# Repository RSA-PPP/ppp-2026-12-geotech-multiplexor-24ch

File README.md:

# ppp-2026-13-geotech-multiplexor-24ch

> **Red Sísmica del Austro (RSA) — Universidad de Cuenca**  
> Prácticas Preprofesionales (PPP) • Sistemas Embebidos, Instrumentación Geotécnica y Control Electromecánico

---

## 📋 Ficha Técnica del Proyecto

| Campo | Detalle |
| :--- | :--- |
| **Código Institucional** | `RSA-PPP-2026-13` |
| **Nombre del Proyecto** | Sistema de Adquisición Electromecánico Multiplexado para Galgas Extensométricas en Presas (ESP32 y PIC16F628A) |
| **Pasante** | Walter Calderón (`walter.calderon@ucuenca.edu.ec`) |
| **Carrera / Institución** | Ingeniería en Telecomunicaciones — Universidad de Cuenca |
| **Tutor Institucional** | Ing. Milton Muñoz (`milton.munozc@ucuenca.edu.ec`) — RSA |
| **Duración / Horas** | 144 horas (10.5 semanas) • Presencial |
| **Fecha de Ejecución** | 2026-10-01 al 2026-12-18 |
| **Estado** | `En Ejecución` |

---

## 🎯 Descripción General y Objetivos

La Red Sísmica del Austro (RSA) gestiona la auscultación estructural continua de presas hidroeléctricas críticas (como Chanlud y Labrado), donde la monitorización de la estabilidad del cuerpo de presa depende de redes de **galgas extensométricas de 4 hilos** embebidas en el concreto y galerías. Cada sensor entrega dos variables físicas acopladas: **deformación mecánica ($\mu\varepsilon$)** y **temperatura interna ($^\circ\text{C}$)** para compensación térmica.

Para optimizar costos de instrumental analógico de ultra alta resolución, el sistema utiliza un mecanismo de multiplexación electromecánica compuesto por **dos selectores rotativos mecánicos de 12 canales** (totalizando 24 sensores analógicos). Cada selector es gobernado por un motor DC acoplado a encoders ópticos de ranura y referencia absoluta (*Home*). La conmutación entre el modo de deformación y el modo de temperatura se realiza mediante un banco de relés (K1..K5) que reconfigura un puente de Wheatstone conectado al convertidor analógico-digital de 24 bits **HX711**.

Este proyecto implementa una arquitectura distribuida de firmware resiliente y de alta precisión:
* **Controlador Esclavo (Microchip PIC16F628A):** Firmware en C (XC8) para posicionamiento angular determinista por interrupciones, frenado dinámico activo en puente H L293D y parser binario UART a 9600 bps.
* **Nodo Maestro de Gestión (Espressif ESP32-WROOM-32):** Firmware en C++ (PlatformIO) para lectura del HX711, secuenciamiento de relés con tiempos muertos de guarda ($\ge 20\text{ ms}$), datalogger autónomo en MicroSD (FAT32/CSV), pantalla LCD alfanumérica y telemetría por comandos ASCII vía RS-232 (115200 bps).

### Objetivos Clave
1. **Hardware y Diagnóstico de Encoders:** Auditar en osciloscopio las señales digitales de los encoders de ranura y muesca Home, y caracterizar las formas de onda de conmutación del puente H L293D.
2. **Firmware de Posicionamiento (PIC16F628A):** Desarrollar en MPLAB X / XC8 las rutinas de búsqueda de origen (*Homing*), conteo de ranuras por interrupciones y frenado dinámico asistido para evitar deslizamientos por inercia.
3. **Protocolo Inter-Microcontroladores:** Diseñar el enlace serie UART binario robusto con delimitadores y suma de comprobación XOR a 9600 bps con máquina de reintentos y tolerancia a fallos.
4. **Adquisición HX711 y Reconfiguración de Puente:** Desarrollar el driver de lectura diferencial de 24 bits para el HX711 y el secuenciador de relés K1..K5 con tiempos de estabilización (*dead-time* $\ge 20\text{ ms}$).
5. **Datalogger MicroSD, Interfaz LCD y Telemetría RS-232:** Implementar la persistencia local en `DATALOG.CSV`, la pantalla informativa LCD y el protocolo de telemetría exterior compatible con sistemas SCADA.
6. **Barrido Secuencial de 24 Canales y Ensayo en Banco:** Orquestar el ciclo completo de auscultación ($\le 90\text{ s}$ para 24 canales) y evaluar la resiliencia en un ensayo de 100 barridos continuos con resistencias patrón.
7. **Guía de Troubleshooting y Documentación Final:** Redactar el manual de solución de averías electromecánicas e Informe Técnico Final.

> 📄 Para consultar el cronograma detallado semana a semana, la carga horaria y los checkpoints verificables, revisa el [Plan de Trabajo Oficial](docs/planificacion.md).

---

## 🏗️ Arquitectura del Sistema y Flujo de Trabajo

```text
+-----------------------------------------------------------------------------------+
|                        DIAGRAMA DE ARQUITECTURA DISTRIBUIDA                       |
+-----------------------------------------------------------------------------------+
|                                                                                   |
|  [24 Galgas Extensométricas en Presa]                                            |
|         |                                                                         |
|         v                                                                         |
|  [Selectores Rotativos Electromecánicos M1 y M2 (12 canales c/u)]                 |
|         ^                                                                         |
|         | (Acoplamiento Mecánico)                                                 |
|  [2x Motores DC con Encoders Ópticos (sens1 / sens2_Home)]                       |
|         ^                                                                         |
|         | (Driver H-Bridge L293D con Frenado Dinámico)                            |
|  [Microchip PIC16F628A - Esclavo de Motores]                                      |
|         ^                                                                         |
|         | (Enlace UART Binario @ 9600 bps / Checksum XOR)                         |
|         v                                                                         |
|  [Espressif ESP32 - Maestro de Adquisición y Gestión]                             |
|  ├── Secuenciador de Relés K1..K5 (Dead-time >= 20 ms) ---> [Puente Wheatstone]   |
|  ├── Driver ADC Diferencial 24-bit (HX711) <----------------+                     |
|  ├── Datalogger Autónomo MicroSD (Bus SPI / FAT32 / DATALOG.CSV)                  |
|  ├── Interfaz de Operación Local (Pantalla LCD Alfanumérica)                      |
|  └── Puerto Serie de Telemetría RS-232 / SCADA ASCII @ 115200 bps                 |
+-----------------------------------------------------------------------------------+
```

---

## 📂 Estructura del Repositorio

> [!IMPORTANT]
> **Estructura Raíz Inmutable:** Para mantener la coherencia con los lineamientos de la RSA, la estructura de carpetas raíz no debe ser alterada ni renombrada sin previa coordinación con el tutor.

```text
ppp-2026-13-geotech-multiplexor-24ch/
├── data/
│   ├── evidence/              # Capturas oscilográficas, evidencias de frenado y curvas
│   └── raw_samples/           # Volcados de prueba de tarjetas MicroSD (DATALOG.CSV)
│
├── docs/
│   ├── hardware/              # Esquemáticos de placas de relés, motores y pinouts
│   ├── troubleshooting/       # Bitácora de fallas mecánicas, atascos y calibración
│   └── planificacion.md       # Documento rector del plan de trabajo (144h) y checkpoints
│
├── firmware/
│   ├── common/                # Definiciones de tramas binarias UART y constantes globales
│   ├── drivers/               # Librerías de bajo nivel: HX711, LCD, L293D, MicroSD
│   ├── pic16f628a/            # Proyecto MPLAB X / XC8 para control de motores
│   ├── esp32/                 # Proyecto PlatformIO / C++ maestro de adquisición
│   └── tests/                 # Firmwares de verificación de reloj, relés y encoders
│
├── python/
│   ├── scripts/               # Scripts de monitoreo RS-232 y parser de DATALOG.CSV
│   ├── utils/                 # Utilitarios para cálculo de estadísticas y verificación
│   └── requirements.txt       # Dependencias de Python para herramientas de soporte PC
│
├── README.md                  # Este documento
└── .gitignore                 # Exclusiones de Git (MPLAB X, PlatformIO, Python, SO)
```

---

## 🛠️ Herramientas y Requisitos de Desarrollo

* **Hardware / Instrumental:**
  - Microcontroladores Microchip **PIC16F628A** y módulo Espressif **ESP32-WROOM-32**.
  - Programador Microchip **PICkit 3 / 4** o **SNAP** con interfaz ICSP.
  - Driver H-Bridge **L293D** y banco de relés conmutadores K1..K5.
  - ADC diferencial de 24 bits **HX711** y módulo MicroSD SPI.
  - Osciloscopio digital, analizador lógico de 8 canales y multímetro de banco.
  - Caja de décadas de resistencias patrón ($350\,\Omega$ y $120\,\Omega \pm 0.05\%$).
* **Entornos de Desarrollo e IDEs:**
  - **MPLAB X IDE v6.xx** con compilador **Microchip XC8** para el PIC16F628A.
  - **VS Code + PlatformIO** (o ESP-IDF / Arduino Core) para el ESP32.
* **Herramientas de Soporte PC:**
  - Python 3.10+ en entorno virtual (`.venv`):
    ```bash
    pip install -r python/requirements.txt
    ```

---

## 🚀 Puesta en Marcha

### 1. Clonar el Repositorio
```bash
git clone git@github.com-rsa:RSA-PPP/ppp-2026-13-geotech-multiplexor-24ch.git
cd ppp-2026-13-geotech-multiplexor-24ch
```

### 2. Compilación del Firmware del Esclavo (PIC16F628A)
1. Abrir **MPLAB X IDE**.
2. Abrir el proyecto ubicado en `firmware/pic16f628a/`.
3. Seleccionar el compilador **XC8** y la herramienta de programación (**PICkit 3/4**).
4. Compilar (`Clean and Build`) y programar la tarjeta de control de motores vía ICSP.

### 3. Compilación del Firmware del Maestro (ESP32)
1. Abrir **VS Code** con la extensión **PlatformIO**.
2. Abrir la carpeta `firmware/esp32/`.
3. Compilar el proyecto (`PlatformIO: Build`) y subir al módulo vía puerto serie (`PlatformIO: Upload`).

### 4. Herramientas de PC y Telemetría RS-232
```powershell
python -m venv .venv
.\.venv\Scripts\Activate.ps1
pip install -r python/requirements.txt
python python/scripts/scada_monitor.py
```

---

## 🛡️ Reglas de Trabajo y Control de Versiones

Para asegurar la calidad y trazabilidad del proyecto durante las prácticas:

1. **Rama Principal:** La rama activa de trabajo es **`main`**. Realiza commits frecuentes y atómicos al finalizar cada bloque o jornada de trabajo.
2. **Formato de Commits:** Utiliza la convención estándar en minúsculas:
   - `feat: [nueva funcionalidad, driver o máquina de estados implementada]`
   - `fix: [corrección de bug en firmware, protocolo o circuito]`
   - `docs: [actualización de esquemas, pinouts, troubleshooting o informe]`
   - `test: [pruebas de encoders, oscilogramas o calibración con resistencias patrón]`
   - `refactor: [optimización de temporizaciones sin cambio de comportamiento]`
3. **Integridad de Código:** No subas archivos temporales de compilación (`.o`, `.d`, carpetas `build/`, `.pio/`) ni volcados masivos sin comprimir. Apóyate en el archivo `.gitignore`.

---

## 📞 Contacto y Soporte Institucional

* **Tutor Institucional:** Ing. Milton Muñoz (`milton.munozc@ucuenca.edu.ec`)
* **Institución:** [Red Sísmica del Austro (RSA)](https://redsismicaaustro.github.io/RSA-Metodologias) — Universidad de Cuenca

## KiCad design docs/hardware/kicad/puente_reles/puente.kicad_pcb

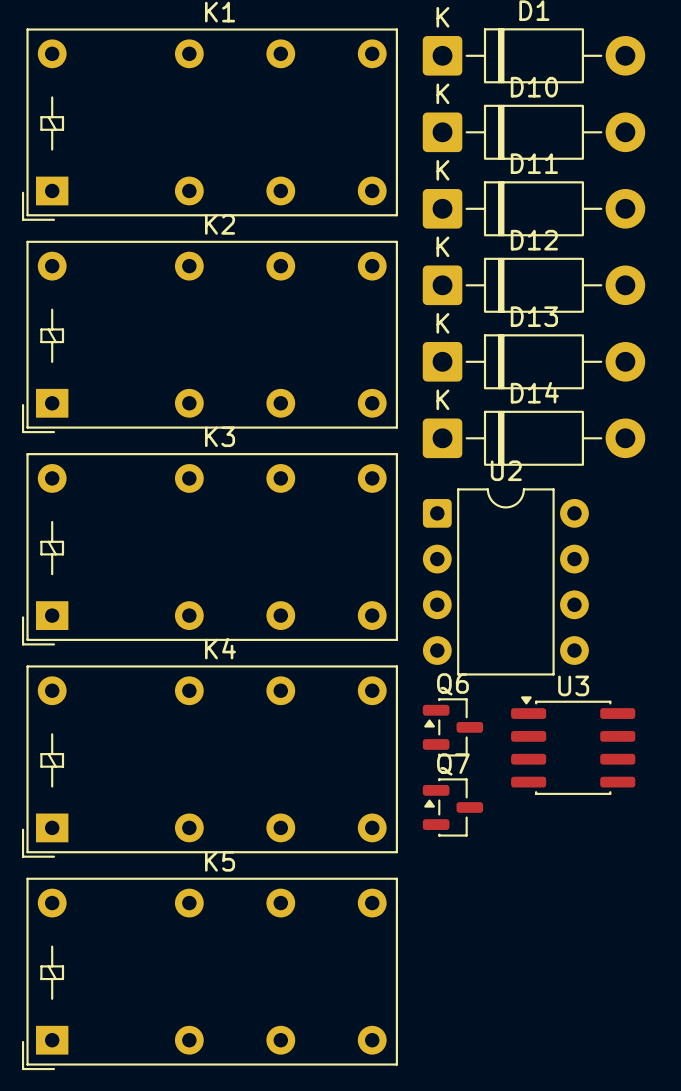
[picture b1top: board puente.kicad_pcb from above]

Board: 2 copper layers, 15 parts (0 on the bottom side), 14 nets, no tracks yet.

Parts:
D1, D10, D11, D12, D13, D14: 1N4007; D_DO-41_SOD81_P10.16mm_Horizontal
K1, K2, K3, K4, K5: HK19F-DCxxV-SHC; Relay_DPDT_Finder_30.22
Q6, Q7: BSS138; SOT-23
U2: DS1307+; DIP-8_W7.62mm
U3: MAX483E; SOIC-8_3.9x4.9mm_P1.27mm

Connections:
/+5V: U2.8 (VCC), U3.8 (VCC)
/+12V: D10.1 (K), D11.1 (K), D12.1 (K), D13.1 (K), D14.1 (K), K1.A1, K2.A1, K3.A1, K4.A1, K5.A1
/IN-: K4.12, K4.24
GND: U2.4 (GND), U3.5 (GND)
unnamed: D10.2 (A), K1.A2
unnamed: D11.2 (A), K2.A2
unnamed: D12.2 (A), K3.A2
unnamed: D13.2 (A), K4.A2
unnamed: D14.2 (A), K5.A2
unnamed: K2.24, K4.22
unnamed: K3.14, K5.11
unnamed: Q6.3 (D), U2.5 (SDA)
unnamed: Q7.3 (D), U2.6 (SCL)
VDD: D1.2 (A), K2.21, Q6.1 (G), Q7.1 (G)

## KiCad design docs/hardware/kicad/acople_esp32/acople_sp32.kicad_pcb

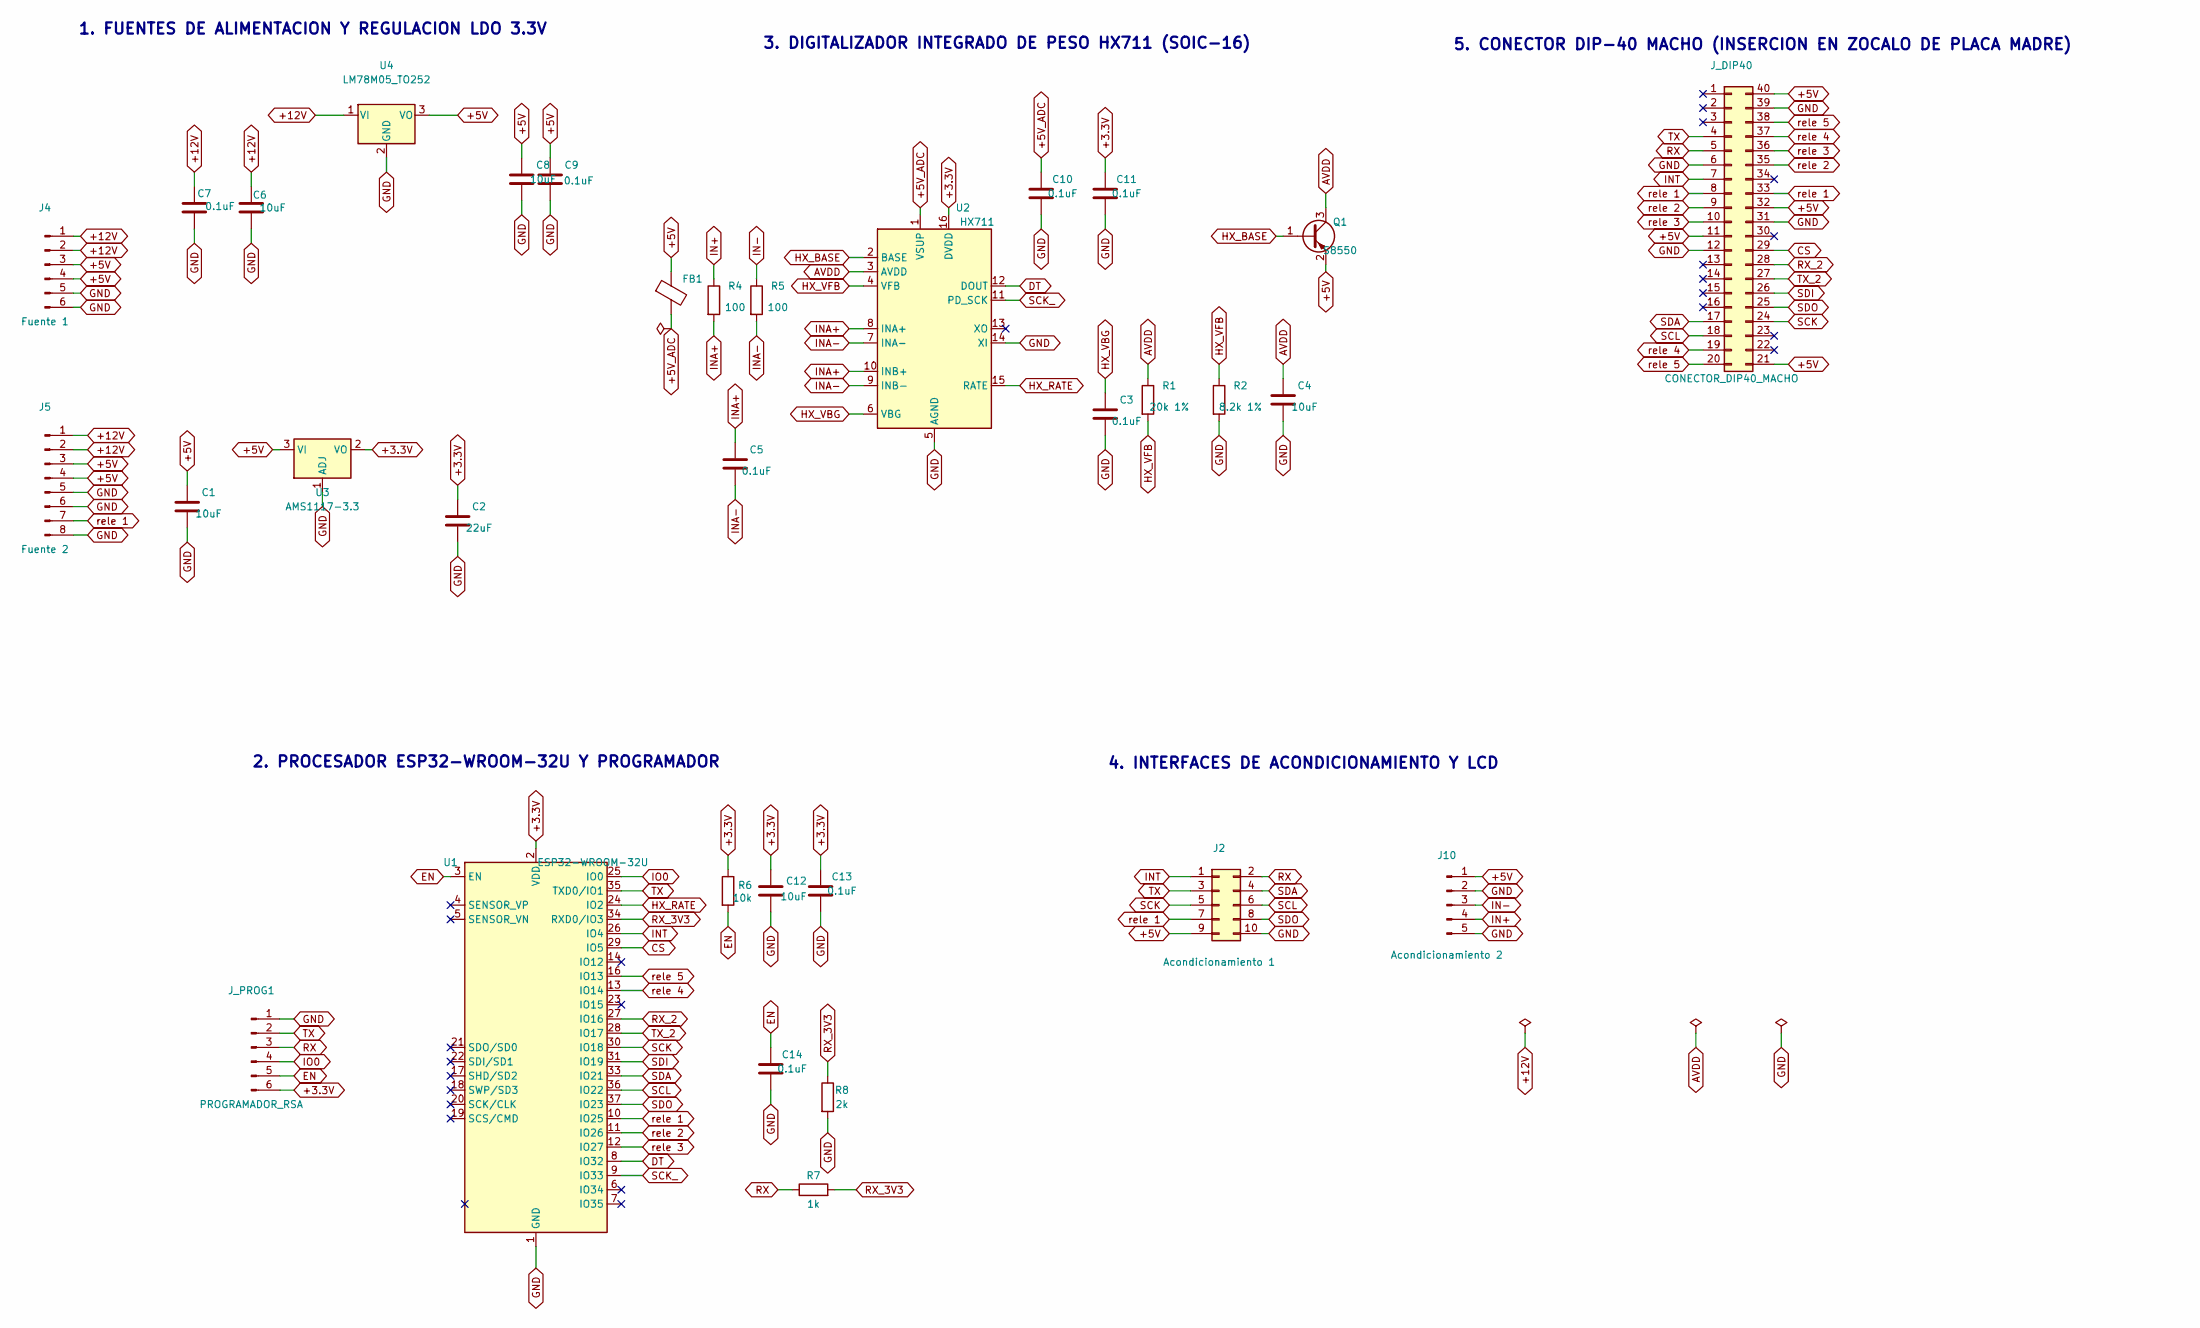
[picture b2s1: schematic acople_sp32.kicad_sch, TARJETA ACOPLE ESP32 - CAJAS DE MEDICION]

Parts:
C1, C4, C6, C8, C12: 10uF; C_0805_2012Metric
C2: 22uF; C_0805_2012Metric
C3, C5, C7, C9, C10, C11, C13, C14: 0.1uF; C_0805_2012Metric
FB1: 600R@100MHz; L_0805_2012Metric
J2: Acondicionamiento 1; PinHeader_2x05_P2.54mm_Vertical
J4: Fuente 1; PinHeader_1x06_P2.54mm_Vertical
J5: Fuente 2; PinHeader_1x08_P2.54mm_Vertical
J10: Acondicionamiento 2; PinHeader_1x05_P2.54mm_Vertical
J_DIP40: CONECTOR_DIP40_MACHO; DIP-40_W15.24mm
J_PROG1: PROGRAMADOR_RSA; PinHeader_1x06_P2.54mm_Vertical
Q1: S8550; SOT-23
R1: 20k 1%; R_0805_2012Metric
R2: 8.2k 1%; R_0805_2012Metric
R4, R5: 100; R_0805_2012Metric
R6: 10k; R_0805_2012Metric
R7: 1k; R_0805_2012Metric
R8: 2k; R_0805_2012Metric
U1: ESP32-WROOM-32U
U2: HX711; SOIC-16_3.9x9.9mm_P1.27mm
U3: AMS1117-3.3; SOT-223-3_TabPin2
U4: LM78M05_TO252; TO-252-3_TabPin2

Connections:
+3.3V: C2.1, C11.1, C12.1, C13.1, J_PROG1.6, R6.1, U1.2 (VDD), U2.16 (DVDD), U3.2 (VO)
+5V: C1.1, C8.1, C9.1, FB1.1, J2.9, J4.3, J4.4, J5.3, J5.4, J10.1, J_DIP40.11, J_DIP40.21, J_DIP40.32, J_DIP40.40, Q1.2 (E), U3.3 (VI), U4.3 (VO)
+5V_ADC: C10.1, FB1.2, U2.1 (VSUP)
+12V: C6.1, C7.1, J4.1, J4.2, J5.1, J5.2, U4.1 (VI)
AVDD: C4.1, Q1.3 (C), R1.1, U2.3 (AVDD)
CS: J_DIP40.29, U1.29 (IO5)
DT: U1.8 (IO32), U2.12 (DOUT)
EN: C14.1, J_PROG1.5, R6.2, U1.3 (EN)
GND: C1.2, C2.2, C3.2, C4.2, C6.2, C7.2, C8.2, C9.2, C10.2, C11.2, C12.2, C13.2, C14.2, J2.10, J4.5, J4.6, J5.5, J5.6, J5.8, J10.2, J10.5, J_DIP40.6, J_DIP40.12, J_DIP40.31, J_DIP40.39, J_PROG1.1, R2.2, R8.2, U1.1 (GND), U1.15 (GND), U1.38 (GND), U1.39 (GND), U2.5 (AGND), U2.14 (XI), U3.1 (ADJ), U4.2 (GND)
HX_BASE: Q1.1 (B), U2.2 (BASE)
HX_RATE: U1.24 (IO2), U2.15 (RATE)
HX_VBG: C3.1, U2.6 (VBG)
HX_VFB: R1.2, R2.1, U2.4 (VFB)
IN+: J10.4, R4.1
IN-: J10.3, R5.1
INA+: C5.1, R4.2, U2.8 (INA+), U2.10 (INB+)
INA-: C5.2, R5.2, U2.7 (INA-), U2.9 (INB-)
INT: J2.1, J_DIP40.7, U1.26 (IO4)
IO0: J_PROG1.4, U1.25 (IO0)
RX: J2.2, J_DIP40.5, J_PROG1.3, R7.1
RX_2: J_DIP40.28, U1.27 (IO16)
RX_3V3: R7.2, R8.1, U1.34 (RXD0/IO3)
SCK: J2.5, J_DIP40.24, U1.30 (IO18)
SCK_: U1.9 (IO33), U2.11 (PD_SCK)
SCL: J2.6, J_DIP40.18, U1.36 (IO22)
SDA: J2.4, J_DIP40.17, U1.33 (IO21)
SDI: J_DIP40.26, U1.31 (IO19)
SDO: J2.8, J_DIP40.25, U1.37 (IO23)
TX: J2.3, J_DIP40.4, J_PROG1.2, U1.35 (TXD0/IO1)
TX_2: J_DIP40.27, U1.28 (IO17)
rele 1: J2.7, J5.7, J_DIP40.8, J_DIP40.33, U1.10 (IO25)
rele 2: J_DIP40.9, J_DIP40.35, U1.11 (IO26)
rele 3: J_DIP40.10, J_DIP40.36, U1.12 (IO27)
rele 4: J_DIP40.19, J_DIP40.37, U1.13 (IO14)
rele 5: J_DIP40.20, J_DIP40.38, U1.16 (IO13)

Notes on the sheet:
2. PROCESADOR ESP32-WROOM-32U Y PROGRAMADOR
1. FUENTES DE ALIMENTACION Y REGULACION LDO 3.3V
5. CONECTOR DIP-40 MACHO (INSERCION EN ZOCALO DE PLACA MADRE)
4. INTERFACES DE ACONDICIONAMIENTO Y LCD
3. DIGITALIZADOR INTEGRADO DE PESO HX711 (SOIC-16)

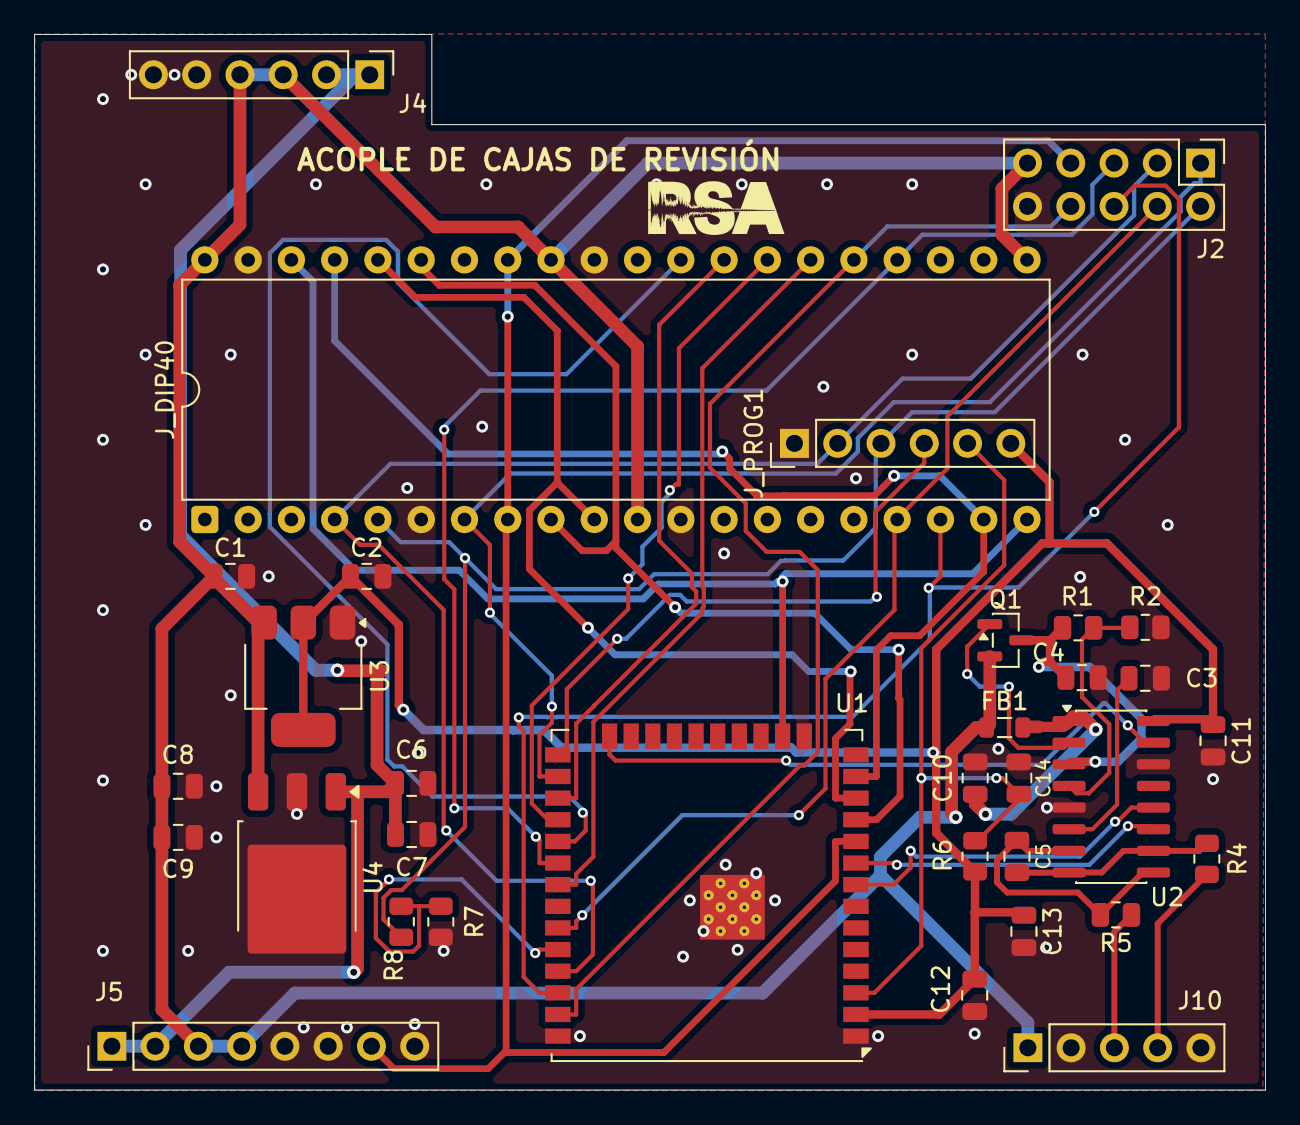
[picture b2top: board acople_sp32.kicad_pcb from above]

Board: 2 copper layers, 72.3 x 62.0 mm, 35 parts (1 on the bottom side), 35 nets.

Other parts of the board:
LOGO_B: Logo_RSA; Logo_RSA_Grande
LOGO_F: Logo_RSA

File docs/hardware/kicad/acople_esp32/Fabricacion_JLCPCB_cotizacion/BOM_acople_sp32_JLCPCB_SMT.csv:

Comment,Designator,Footprint,LCSC Part #,Type
10uF 25V X5R,"C1, C4, C6, C8, C12",C_0805_2012Metric,C15850,Basic Part / Extended
22uF 16V X5R,C2,C_0805_2012Metric,C44026,Extended Part
0.1uF 50V X7R,"C3, C5, C7, C9, C10, C11, C13, C14",C_0805_2012Metric,C49678,Basic Part
600R@100MHz 2A,FB1,L_0805_2012Metric,C1015,Basic Part
S8550 PNP (2TY),Q1,SOT-23,C2146,Basic Part
20k 1%,R1,R_0805_2012Metric,C26002,Extended Part
8.2k 1%,R2,R_0805_2012Metric,C26081,Extended Part
100R 1%,"R4, R5",R_0805_2012Metric,C17462,Basic Part
10k 1%,R6,R_0805_2012Metric,C17414,Basic Part
1k 1%,R7,R_0805_2012Metric,C17513,Basic Part
2k 1%,R8,R_0805_2012Metric,C17538,Extended Part
ESP32-WROOM-32U-N4,U1,ESP32-WROOM-32U,C328062,Extended Part
HX711 24-bit ADC,U2,SOIC-16_3.9x9.9mm_P1.27mm,C43656,Extended Part
AMS1117-3.3,U3,SOT-223-3_TabPin2,C6186,Basic Part
CJ78M05 5V 500mA,U4,TO-252-3_TabPin2,C9070,Extended Part
